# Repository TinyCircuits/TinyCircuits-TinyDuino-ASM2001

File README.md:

# TinyCircuits TinyDuino Processor Board
# ASM2001 Rev9

The design files are located under design_files/  for the TinyCircuits ASM2001 Rev 9 PCB.  This is a Tiny processor board (Square Version, 20mm x 20mm) that uses the same microcontroller (Atmel Atmega328P) as the Arduino Uno and has stackable TinyShield support.  

Format is in Cadsoft Eagle format - Eagle version 6.2 was used for the original design.

For more infomation on this, check out the product page at Tiny-Circuits.com: https://tinycircuits.com/collections/processors/products/tinyduino-processor-board

# License:

Design by TinyCircuits.
All design files are released under the Creative Commons Attribution Share-Alike 3.0 License, see the following link for details: http://creativecommons.org/licenses/by-sa/3.0

All text above must be included in any redistribution or derived design

This project uses designs and concepts developed as part of the Arduino project and the LilyPad project.  The TinyCircuits design files themselves (schematics, PCB and libraries) are not directly derived from these works' design files and have been created new, however the concepts and basic architecture behind the TinyDuino and TinyLily products are derived and we thank the hard work of the organizations below for their contributions to open-source hardware:
  
Original Arduino Uno Design by Team Arduino

LilyPad Arduino Design by Leah Buechley and Sparkfun Electronics

Please support the open-source hardware community

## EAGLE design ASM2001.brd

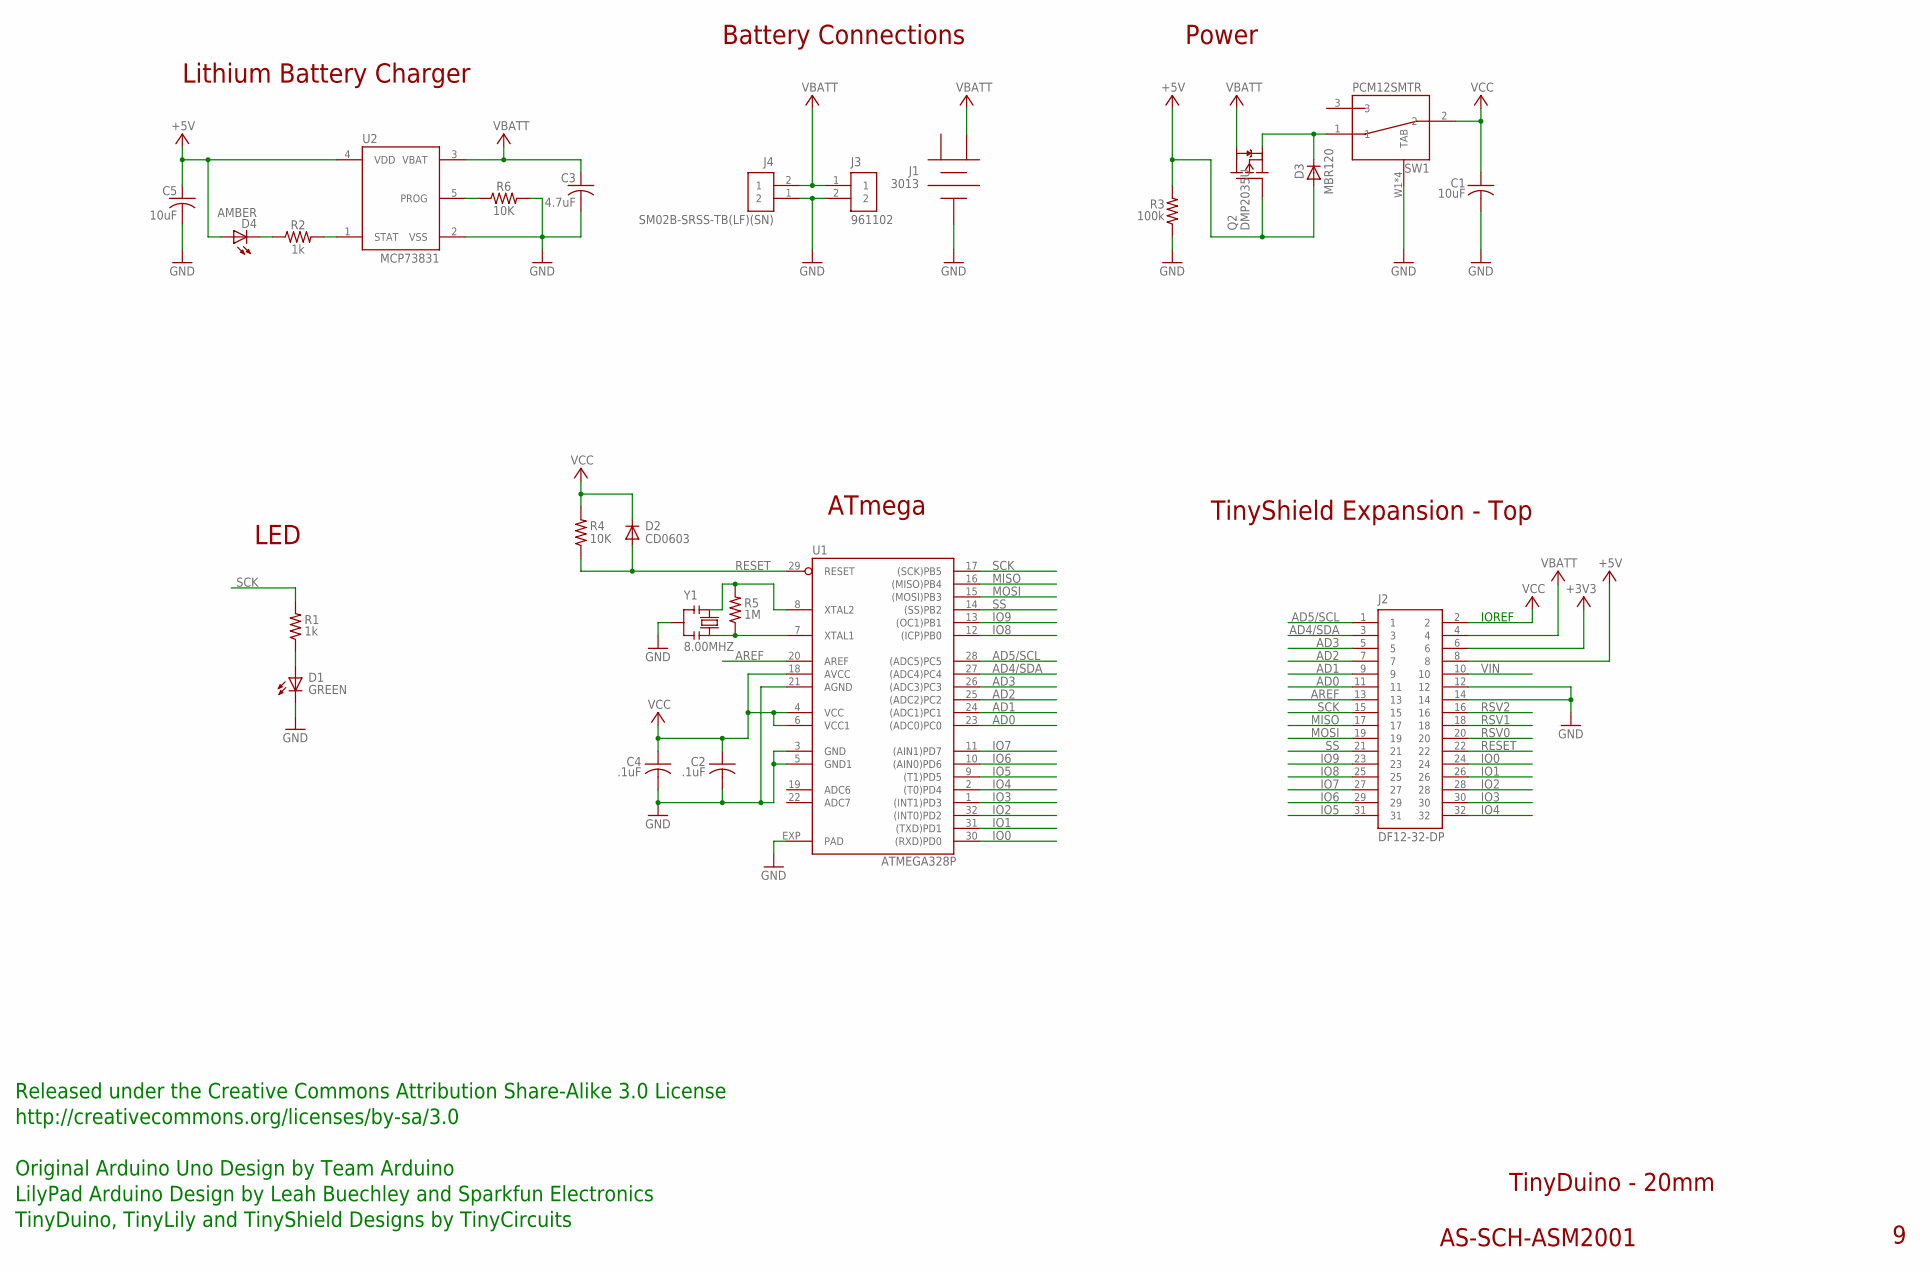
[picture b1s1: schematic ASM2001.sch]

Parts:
C1, C5: 10uF; C0603; PARTNO AS-ITM-00002
C2, C4: .1uF; C0402; PARTNO AS-ITM-00008
C3: 4.7uF; C0402; PARTNO AS-ITM-00242
D1: GREEN; LNJ_LED; PARTNO AS-ITM-00011
D2: CD0603; 0603; PARTNO AS-ITM-00009
D3: MBR120; SOD-123FL
D4: AMBER; LNJ_LED; PARTNO AS-ITM-00026
J1: 3013; PARTNO AS-ITM-00001
J2: DF12-32-DP; PARTNO AS-ITM-00015
J3: 961102; 2X.1"
J4: SM02B-SRSS-TB(LF)(SN); JST_SH_2X1
Q2: DMP2035U; SOT23
R1, R2: 1k; 0402; PARTNO AS-ITM-00003
R3: 100k; 0402; PARTNO AS-ITM-00004
R4: 10K; 0402; PARTNO AS-ITM-00032
R5: 1M; 0402; PARTNO AS-ITM-00005
R6: 10K; 0402
SW1: PCM12SMTR
U1: ATMEGA328P; ATMEL_QFN32; PARTNO AS-ITM-00013
U2: MCP73831; SOT-23
Y1: 8.00MHZ; RESONATOR_SMALL; PARTNO AS-ITM-00027

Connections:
1: J1.1
+3V3: J2.6
+5V: C5.1, D3.A, D4.A, J2.8, Q2.B (G), R3.2, U2.4 (VDD)
AD0: J2.11, U1.23 ((ADC0)PC0)
AD1: J2.9, U1.24 ((ADC1)PC1)
AD2: J2.7, U1.25 ((ADC2)PC2)
AD3: J2.5, U1.26 ((ADC3)PC3)
AD4/SDA: J2.3, U1.27 ((ADC4)PC4)
AD5/SCL: J2.1, U1.28 ((ADC5)PC5)
AREF: J2.13, U1.20 (AREF)
GND: C1.2, C2.2, C3.2, C4.2, C5.2, D1.C, J1.3, J2.12, J2.14, J3.2, J4.1 (2), R3.1, R6.2, SW1.W1 (TAB), SW1.W2 (TAB), SW1.W3 (TAB), SW1.W4 (TAB), U1.3 (GND), U1.5 (GND1), U1.21 (AGND), U1.EXP (PAD), U2.2 (VSS), Y1.2
IO0: J2.24, U1.30 ((RXD)PD0)
IO1: J2.26, U1.31 ((TXD)PD1)
IO2: J2.28, U1.32 ((INT0)PD2)
IO3: J2.30, U1.1 ((INT1)PD3)
IO4: J2.32, U1.2 ((T0)PD4)
IO5: J2.31, U1.9 ((T1)PD5)
IO6: J2.29, U1.10 ((AIN0)PD6)
IO7: J2.27, U1.11 ((AIN1)PD7)
IO8: J2.25, U1.12 ((ICP)PB0)
IO9: J2.23, U1.13 ((OC1)PB1)
MISO: J2.17, U1.16 ((MISO)PB4)
MOSI: J2.19, U1.15 ((MOSI)PB3)
unnamed: R5.2, U1.8 (XTAL2), Y1.1
unnamed: D3.C, Q2.E (S), SW1.1
unnamed: R5.1, U1.7 (XTAL1), Y1.3
unnamed: D1.A, R1.1
unnamed: D4.C, R2.1
unnamed: R6.1, U2.5 (PROG)
unnamed: R2.2, U2.1 (STAT)
RESET: D2.A, J2.22, R4.1, U1.29 (RESET)
RSV0: J2.20
RSV1: J2.18
RSV2: J2.16
SCK: J2.15, R1.2, U1.17 ((SCK)PB5)
SS: J2.21, U1.14 ((SS)PB2)
VBATT: C3.1, J1.2, J2.4, J3.1, J4.2 (1), Q2.C (D), U2.3 (VBAT)
VCC: C1.1, C2.1, C4.1, D2.C, J2.2, R4.2, SW1.2, U1.4 (VCC), U1.6 (VCC1), U1.18 (AVCC)
VIN: J2.10

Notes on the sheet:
IOREF
TinyShield Expansion - Top
ATmega
Power
LED
TinyDuino - 20mm
AS-SCH-ASM2001
Released under the Creative Commons Attribution Share-Alike 3.0 License
http://creativecommons.org/licenses/by-sa/3.0
Original Arduino Uno Design by Team Arduino
TinyDuino, TinyLily and TinyShield Designs by TinyCircuits
LilyPad Arduino Design by Leah Buechley and Sparkfun Electronics
Lithium Battery Charger
Battery Connections

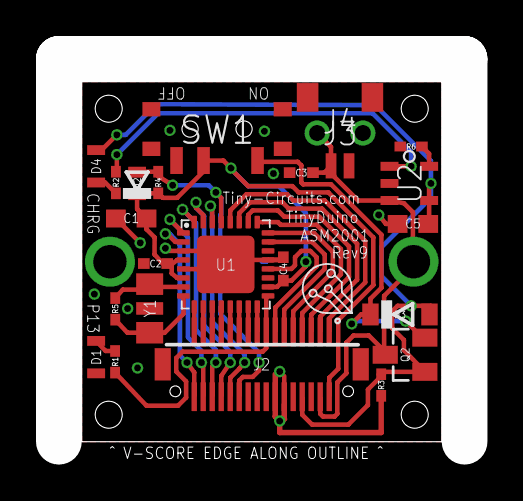
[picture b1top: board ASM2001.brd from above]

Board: 2 copper layers, 20.0 x 20.0 mm, 25 parts (1 on the bottom side), 33 nets.

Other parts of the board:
U$1: DOCFIELD-TINYCIRCUITS-PCB

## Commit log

2012-08-28 Initial Commit of Rev 4 version of ASM2001
2013-06-30 Updated project link
2013-12-22 Updated to Rev6
2014-08-24 Updated Link
2015-02-21 Updated to Rev 8
2016-02-02 Update to Rev 9
2019-01-02 Update format
2019-02-01 add tutorial images
2019-05-22 added images
2020-02-11 image update
2020-06-26 Add CAD data
2020-06-29 Rename files, add dxf, use new 2D drawing template
2020-07-01 Remove vias in models & drawings, add compact dimension images, and remove a file to reduce size
2020-07-02 Add zip of all CAD files
2020-08-18 Update CAD drawings
